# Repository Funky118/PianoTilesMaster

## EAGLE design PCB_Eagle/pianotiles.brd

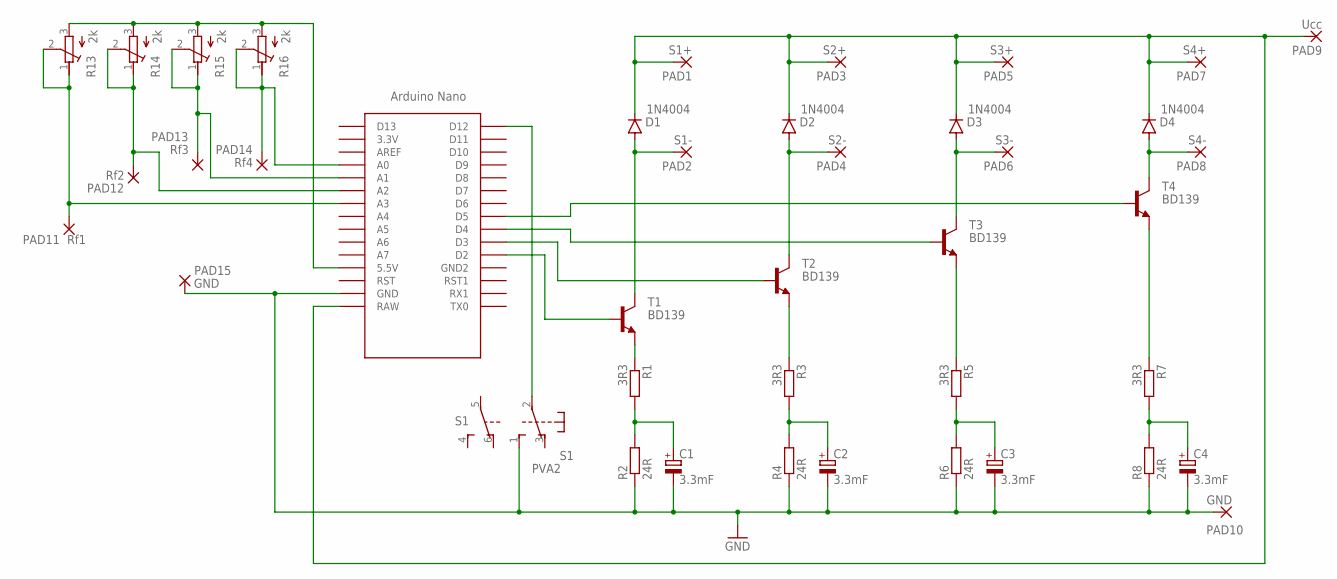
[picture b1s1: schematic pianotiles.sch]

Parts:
C1, C2, C3, C4: 3.3mF; E5-10,5
D1, D2, D3, D4: 1N4004; DO41-10
PAD1: S1+; 2,15/1,0
PAD2: S1-; 2,15/1,0
PAD3: S2+; 2,15/1,0
PAD4: S2-; 2,15/1,0
PAD5: S3+; 2,15/1,0
PAD6: S3-; 2,15/1,0
PAD7: S4+; 2,15/1,0
PAD8: S4-; 2,15/1,0
PAD9: Ucc; 2,54/1,0
PAD10: GND; 2,54/1,0
PAD11: Rf1; 2,15/1,0
PAD12: Rf2; 2,15/1,0
PAD13: Rf3; 2,15/1,0
PAD14: Rf4; 2,15/1,0
PAD15: GND; 2,15/1,0
R1, R3, R5, R7: 3R3; 0309/10
R2, R4, R6, R8: 24R; 0309/10
R13, R14, R15, R16: 2k; RTRIMT93YA
S1: PVA2; PVA2F
T1, T2, T3, T4: BD139; TO126
U$1: NANO

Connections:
GND: C1.-, C2.-, C3.-, C4.-, PAD10.1, PAD15.1, R2.1, R4.1, R6.1, R8.1, S1.1 (S), U$1.GND
unnamed: C2.+, R3.2, R4.2
unnamed: C1.+, R1.2, R2.2
unnamed: R1.1, T1.1 (E)
unnamed: R3.1, T2.1 (E)
unnamed: T4.3 (B), U$1.D5
unnamed: D2.A, PAD4.1, T2.2 (C)
unnamed: T3.3 (B), U$1.D4
unnamed: C3.+, R5.2, R6.2
unnamed: R5.1, T3.1 (E)
unnamed: T2.3 (B), U$1.D3
unnamed: D3.A, PAD6.1, T3.2 (C)
unnamed: PAD11.1, R13.1 (E), R13.2 (S), U$1.A3
unnamed: D1.C, D2.C, D3.C, D4.C, PAD1.1, PAD3.1, PAD5.1, PAD7.1, PAD9.1, U$1.RAW
unnamed: D1.A, PAD2.1, T1.2 (C)
unnamed: S1.2, U$1.D12
unnamed: C4.+, R7.2, R8.2
unnamed: R7.1, T4.1 (E)
unnamed: T1.3 (B), U$1.D2
unnamed: D4.A, PAD8.1, T4.2 (C)
unnamed: PAD12.1, R14.1 (E), R14.2 (S), U$1.A2
unnamed: PAD13.1, R15.1 (E), R15.2 (S), U$1.A1
unnamed: PAD14.1, R16.1 (E), R16.2 (S), U$1.A0
unnamed: R13.3 (A), R14.3 (A), R15.3 (A), R16.3 (A), U$1.5V (5.5V)

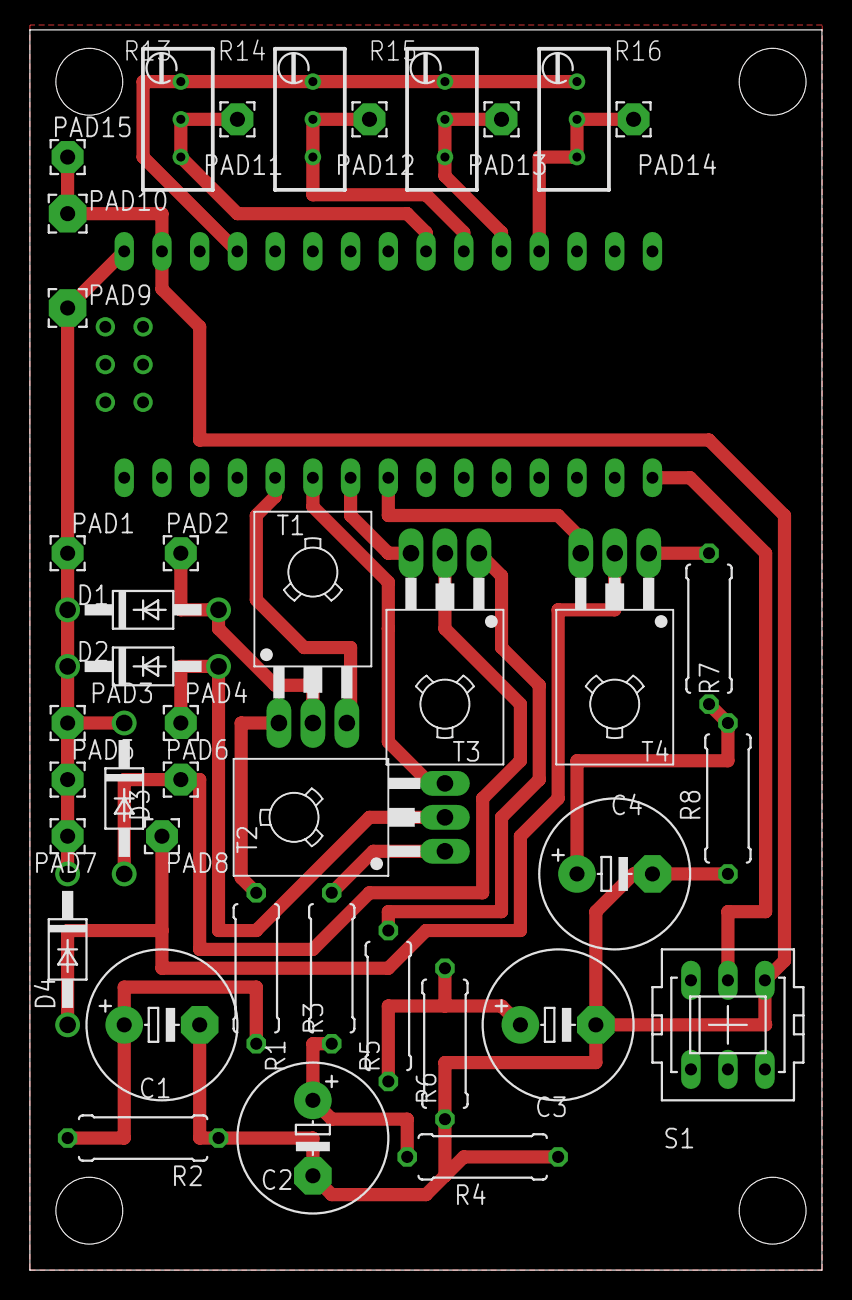
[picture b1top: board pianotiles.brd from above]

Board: 2 copper layers, 53.3 x 83.5 mm, 41 parts (0 on the bottom side), 24 nets.

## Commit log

2019-04-06 first com
2019-04-06 adding readme
2019-04-06 Rename readme.txt to readme.md
2019-04-13 codes finished nows the time for tuning
2019-04-14 added pushCheck and pullCheck methods as well as made all sensor/actuator couples functional
2019-04-15 changed readme
2019-04-15 change to readme
2019-04-16 some bug fixes
2019-04-20 added: reset method, output pin for signal diode, also some bug fixes
2019-04-21 IT WHERKS!
2019-04-21 The vijeo was too humongous
2019-04-28 Proposal of driving circuit for solenoid in matlab
2019-04-28 Adding library with Arduino models
2019-04-28 Adding Eagle schematic
2019-04-28 Final proposal of created PCB
2019-04-29 Adding mechanical part of project
2019-04-30 Adding core of documentation
2019-04-30 Documentation v1.1
2019-04-30 Adding datasheets of solenoid and transistor
2019-04-30 Documentation v1.11
2019-05-01 Adding modified blueprint of "pouzdro"
2019-05-01 Documentation v1.2
2019-05-01 Creating folder for Dominiks c++ sources
2019-05-01 added my share to the tex file, change names to look more pretty
2019-05-01 added my share to tex file, changed folder names to look more pretty
2019-05-01 Last version of documentation
2019-05-01 pdf version of documentation s Please enter the commit message for your changes. Lines starting
2019-05-08 some bug fixes as well as a preview
